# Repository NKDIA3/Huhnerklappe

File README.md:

# Huhnerklappe
Abschlussprojekt

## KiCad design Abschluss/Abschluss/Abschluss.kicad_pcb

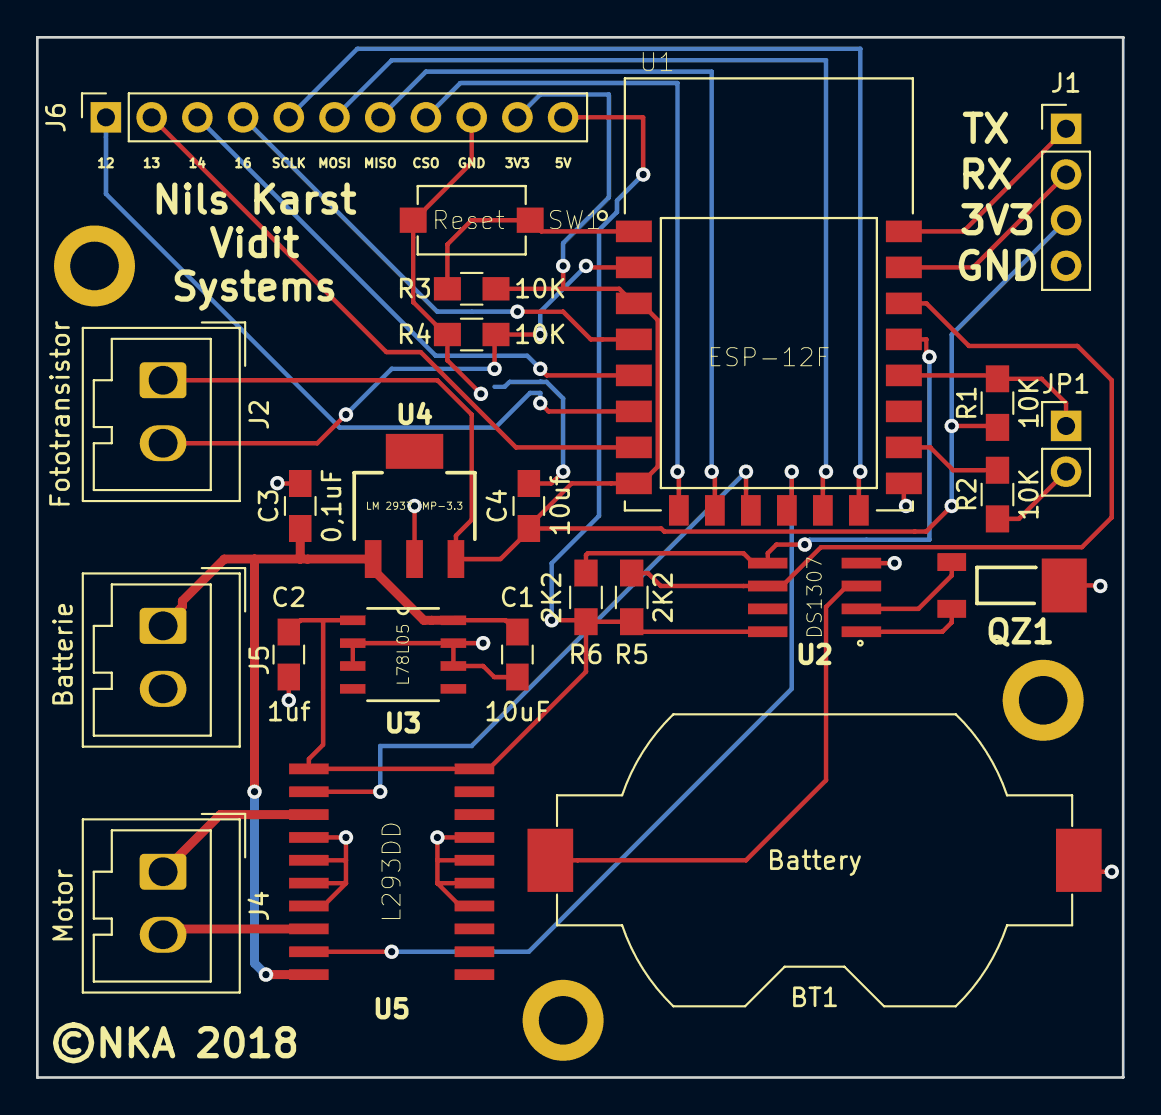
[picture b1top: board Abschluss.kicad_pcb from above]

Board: 2 copper layers, 60.3 x 57.8 mm, 24 parts (0 on the bottom side), 27 nets.

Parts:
BT1: Battery; Keystone_1058_1x2032-CoinCell
C1: 10uF; C_0805_HandSoldering
C2: 1uf; C_0805_HandSoldering
C3: 0,1uF; C_0805_HandSoldering
C4: 10uf; C_0805_HandSoldering
J1: Conn_01x04; Pin_Header_Straight_1x04_Pitch2.54mm
J2: Fototransistor; Wago_734-132_1x02_P3.50mm_Vertical
J4: Motor; Wago_734-132_1x02_P3.50mm_Vertical
J5: Batterie; Wago_734-132_1x02_P3.50mm_Vertical
J6: Erweiterung; PinSocket_1x11_P2.54mm_Vertical
JP1: Prog; Pin_Header_Straight_1x02_Pitch2.54mm
QZ1: MS1V-T1K32
R1, R2, R3, R4: 10K; R_0805_HandSoldering
R5, R6: 2K2; R_0805_HandSoldering
SW1: Reset; 434111025826
U1: ESP-12F; XCVR_ESP8266-12E%2fESP-12E
U2: DS1307; SO08
U3: L78L05; SOIC127P600X175-8N
U4: LM 2937 IMP-3.3; SOT230P700X180-4N
U5: L293DD; SO20

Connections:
3V3: C4.1, J1.3, J2.1, J6.10, R1.1, R3.2, U1.3, U1.8, U4.3
5V: C2.1, J6.11, R5.1, R6.1, U2.8, U3.1, U5.1, U5.20
12V: C1.1, C3.1, J5.1, U3.8, U4.1, U5.10
ADC: J2.2, R4.1, U1.2
CSO: J6.8, U1.9
GND: BT1.2, C1.2, C2.2, C3.2, C4.2, J1.4, J5.2, J6.9, JP1.2, QZ1.1, R2.1, R4.2, SW1.1, U1.15, U2.4, U3.2, U3.3, U3.6, U3.7, U4.2, U5.4, U5.5, U5.6, U5.7, U5.14, U5.15, U5.16, U5.17
GPIO9: U1.11, U5.2
GPIO10: U1.12, U5.9
GPIO12: J6.1, U1.6
GPIO13: J6.2, U1.7
GPIO14: J6.3, U1.5
GPIO16: J6.4, U1.4
MISO: J6.7, U1.10
MOSI: J6.6, U1.13
unnamed: BT1.1, U2.3
unnamed: J4.1, U5.3
unnamed: J4.2, U5.8
unnamed: JP1.1, R1.2, U1.18
unnamed: QZ1.2, U2.1
unnamed: QZ1.3, U2.2
unnamed: R2.2, U1.16
unnamed: R3.1, SW1.2, U1.1
RX: J1.2, U1.21
SCL: R5.2, U1.20, U2.6
SCLK: J6.5, U1.14
SDA: R6.2, U1.19, U2.5
TX: J1.1, U1.22

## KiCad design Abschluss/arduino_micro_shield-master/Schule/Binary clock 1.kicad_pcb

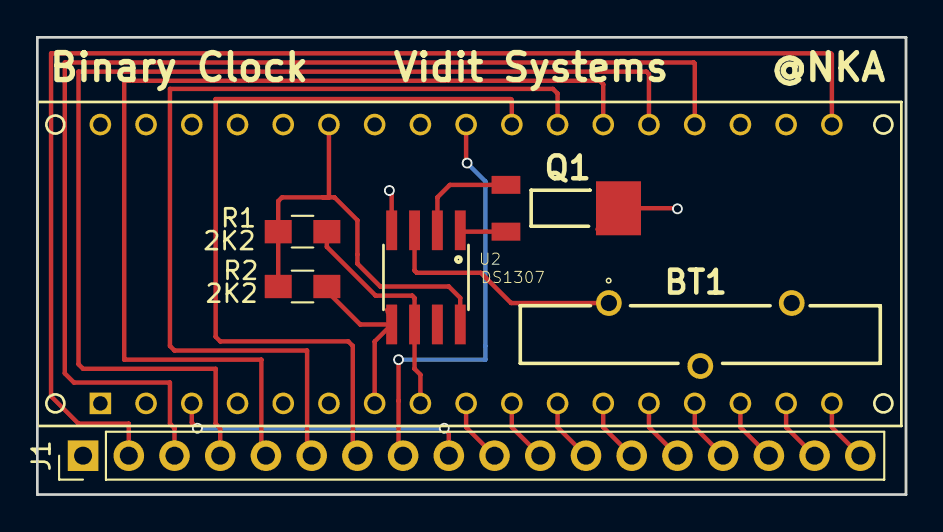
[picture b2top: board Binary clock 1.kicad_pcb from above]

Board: 2 copper layers, 48.3 x 25.4 mm, 6 parts (0 on the bottom side), 7 nets.

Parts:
BT1: CR2032MFR-RV
J1: Conn_01x18_Male; Pin_Header_Straight_1x18_Pitch2.54mm
Q1: MS1V-T1K32
R1, R2: 2K2; R_0805_HandSoldering
U2: DS1307; SO08

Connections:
GND: BT1.2, J1.1, Q1.1, U2.4
unnamed: BT1.1, U2.3
unnamed: Q1.2, U2.1
unnamed: Q1.3, U2.2
unnamed: R1.1, R2.1, U2.8
unnamed: R1.2, U2.6
unnamed: R2.2, U2.5

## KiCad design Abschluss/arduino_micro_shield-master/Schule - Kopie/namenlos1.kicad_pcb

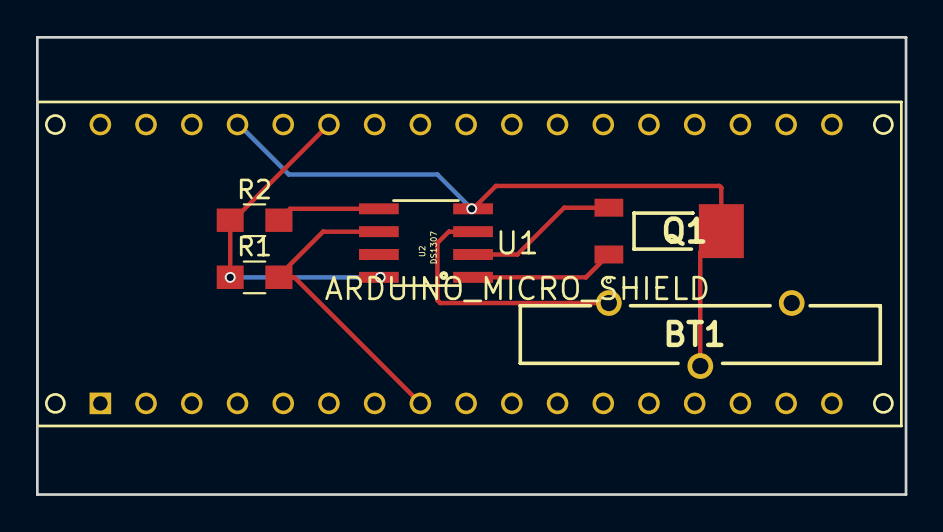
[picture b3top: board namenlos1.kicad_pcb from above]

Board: 2 copper layers, 48.3 x 25.4 mm, 6 parts (0 on the bottom side), 7 nets.

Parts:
BT1: CR2032MFR_RV; CR2032MFR-RV
Q1: MS1V-T1K_32.768kHz_7pF_+-20ppm; MS1V-T1K32
R1, R2: 2K2; R_0805_HandSoldering
U1: ARDUINO_MICRO_SHIELD
U2: DS1307; SO08

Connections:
unnamed: BT1.1, BT1.3, U2.3
unnamed: BT1.2, Q1.1, U1.GND, U2.4
unnamed: Q1.2, U2.1
unnamed: Q1.3, U2.2
unnamed: R1.1, R2.1, U1.5V, U2.8
unnamed: R1.2, U1.3, U2.6
unnamed: R2.2, U1.2, U2.5

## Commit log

2019-01-09 Update WIP.ino
    Alle Funktionen enthalten und getestet.
    ---
2019-01-14 Added Doku 0.9
    Doku Abgabe Borg
2019-01-14 Added some Description ESP
2019-01-14 Added Kicad
2019-01-14 Weitere Ergänzungen
2019-01-14 Updated Doku
2019-01-14 Schaltplan optische anpassung
2019-01-15 Added Doku
2019-01-15 Doku V1
2019-01-15 Rechtschreibprüfung
2019-01-16 Rechtschreibung
2019-01-19 Bugfix Abend &
    && durch ||
2019-01-19 Quellcode Doku aktualisiert
    && ||
2019-01-21 SoWi Fragen Ergänzt
2019-01-21 Doku 99%
    Doku fast fertig
    Todo ergänzt
    Datenblätter hinzugefügt
2019-01-22 Doku done
2019-01-22 Doku fix
2019-01-23 Code für Präsentation optimiert
2019-09-05 Create test.txt
    add Dokument

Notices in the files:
Abschluss/Abschluss/Abschluss.kicad_pcb:
©NKA 2018
